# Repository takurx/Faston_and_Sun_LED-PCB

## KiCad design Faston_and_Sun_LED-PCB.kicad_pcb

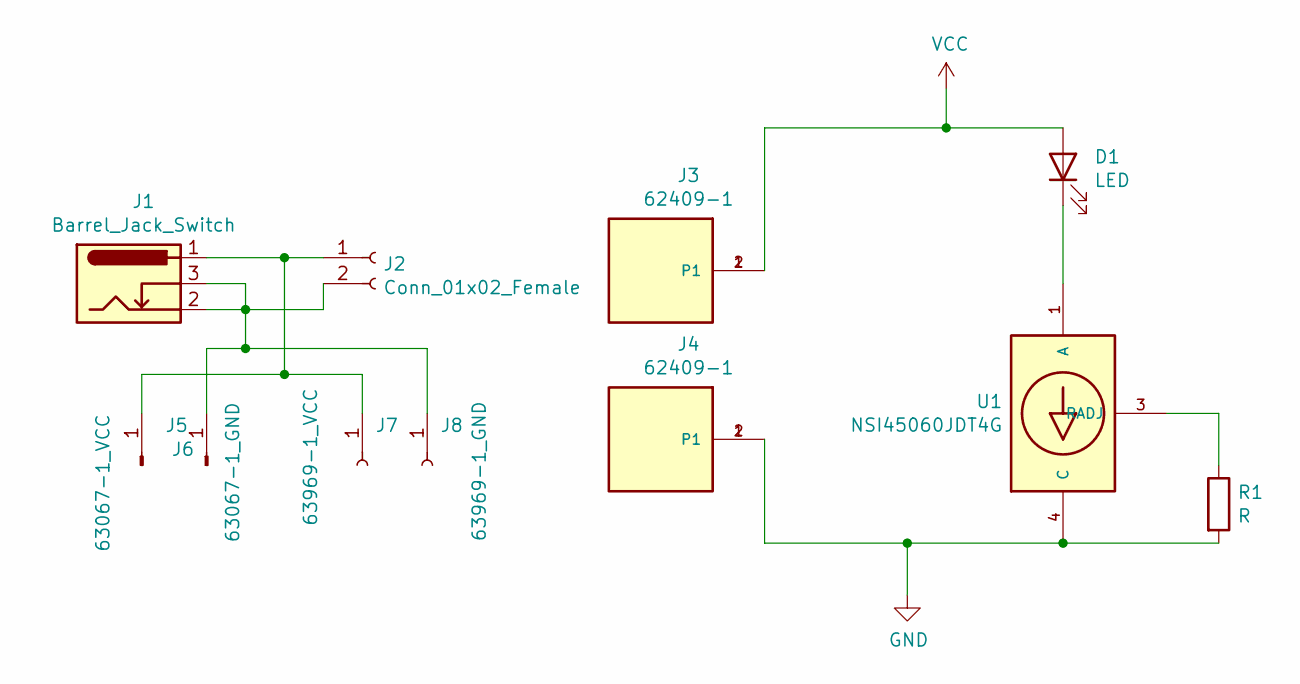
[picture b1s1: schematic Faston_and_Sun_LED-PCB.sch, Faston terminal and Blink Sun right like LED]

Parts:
D1: LED; ENB01-NHSD7-F1
J1: Barrel_Jack_Switch; BarrelJack_Horizontal
J2: Conn_01x02_Female; PinHeader_1x02_P2.54mm_Vertical
J3, J4: 62409-1; TE_62409-1
J5: 63067-1_VCC; 63067-1
J6: 63067-1_GND; 63067-1
J7: 63969-1_VCC; 63969-1
J8: 63969-1_GND; 63969-1
R1: R; R_Axial_DIN0207_L6.3mm_D2.5mm_P2.54mm_Vertical
U1: NSI45060JDT4G; SOT229P991X238-4N

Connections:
GND: J4.1, J4.2, R1.2, U1.4 (C)
unnamed: D1.1 (K), U1.1 (A)
unnamed: J1.1, J2.1, J5.1, J7.1
unnamed: J1.2, J1.3, J2.2, J6.1, J8.1
unnamed: R1.1, U1.3 (RADJ)
VCC: D1.2 (A), J3.1, J3.2

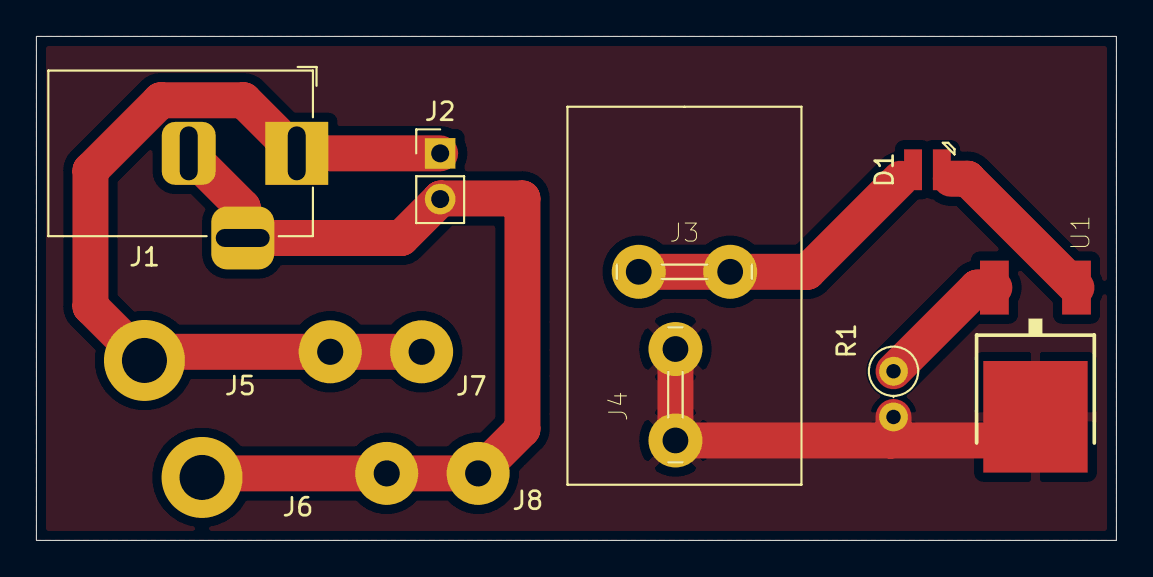
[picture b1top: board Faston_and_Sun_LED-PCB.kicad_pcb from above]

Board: 2 copper layers, 60.0 x 28.0 mm, 11 parts (0 on the bottom side), 6 nets.

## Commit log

2020-11-29 add schematic and library
    add schematic and library
2020-11-29 add pcb v1.0.0
    add pcb v1.0.0
2020-11-29 add V1.0.1 and output gerber
    add V1.0.1 and output gerber
